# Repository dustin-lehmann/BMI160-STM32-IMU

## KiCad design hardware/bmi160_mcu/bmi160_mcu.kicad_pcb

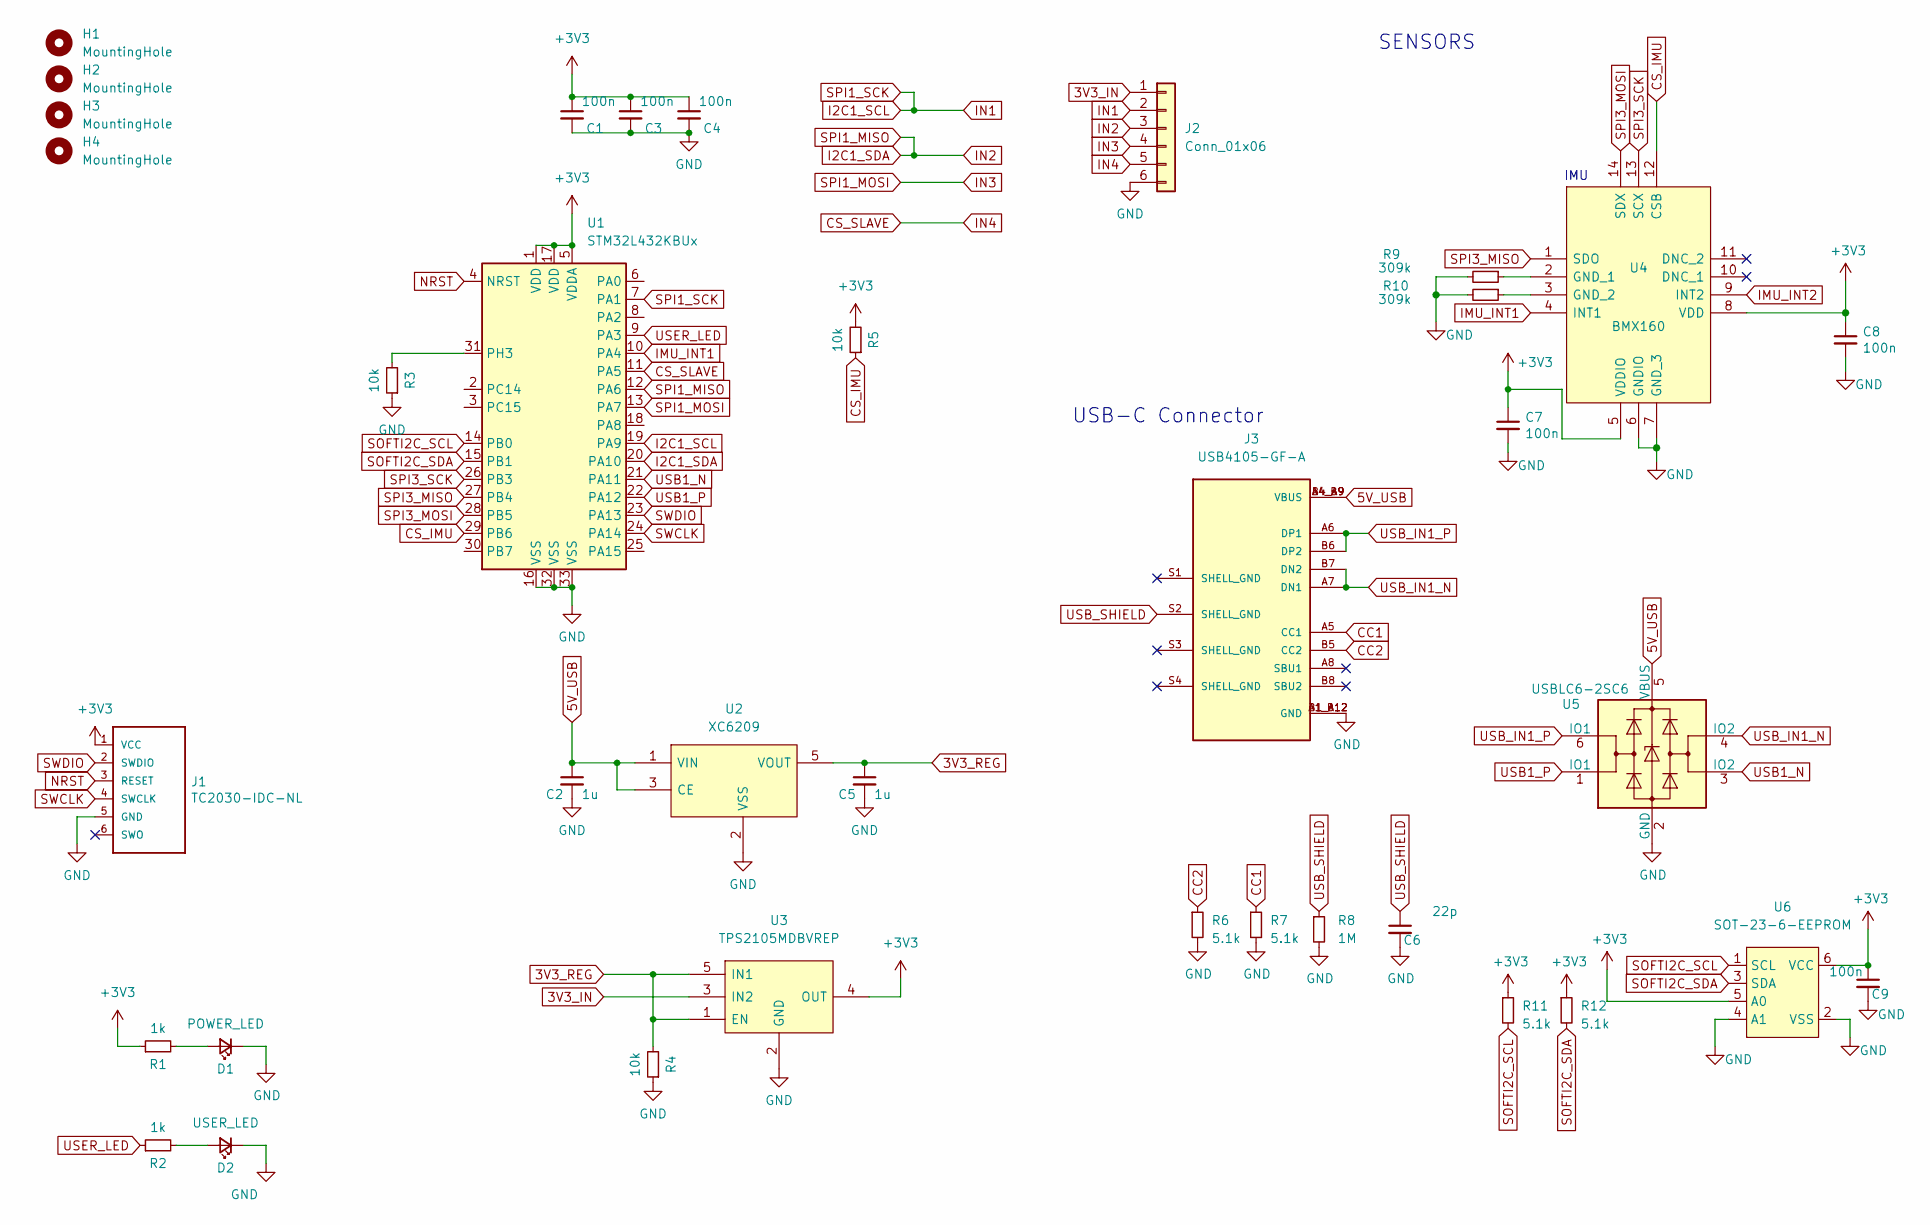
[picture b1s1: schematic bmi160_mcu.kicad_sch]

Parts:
C1, C3, C4, C7, C8, C9: 100n; C_0603_1608Metric
C2, C5: 1u; C_0603_1608Metric
C6: 22p; C_0603_1608Metric
D1: POWER_LED; LED_0603_1608Metric
D2: USER_LED; LED_0603_1608Metric
H1, H2, H3, H4: MountingHole; MH_noPad_2.5
J1: TC2030-IDC-NL; Tag-Connect_TC2030-IDC-NL_2x03_P1.27mm_Vertical
J2: Conn_01x06; JST_GH_SM06B-GHS-TB_1x06-1MP_P1.25mm_Horizontal
J3: USB4105-GF-A; GCT_USB4105-GF-A; PARTREV A3
R1, R2: 1k; R_0603_1608Metric
R3, R4, R5: 10k; R_0603_1608Metric
R6, R7, R11, R12: 5.1k; R_0603_1608Metric
R8: 1M; R_0603_1608Metric
R9, R10: 309k; R_0603_1608Metric
U1: STM32L432KBUx; QFN-32-1EP_5x5mm_P0.5mm_EP3.45x3.45mm
U2: XC6209; SOT95P280X130-5N; Mouser Part Number 865-XC6701B332MR-G
U3: TPS2105MDBVREP; SOT95P280X145-5N; Mouser Part Number 595-TPS2105MDBVREP
U4: BMX160; PQFN50P300X250X88-14N; Mouser Part Number 262-BMX160
U5: USBLC6-2SC6; SOT-23-6
U6: SOT-23-6-EEPROM; SOT-23-6

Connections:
3V3_IN: J2.1, U3.3 (IN2)
3V3_REG: C5.1, R4.2, U2.5 (VOUT), U3.1 (EN), U3.5 (IN1)
5V_USB: C2.1, J3.A4_B9 (VBUS), J3.B4_A9 (VBUS), U2.1 (VIN), U2.3 (CE), U5.5 (VBUS)
+3V3: C1.1, C3.1, C4.1, C7.1, C8.1, C9.1, J1.1 (VCC), R1.1, R5.2, R11.1, R12.1, U1.1 (VDD), U1.5 (VDDA), U1.17 (VDD), U3.4 (OUT), U4.5 (VDDIO), U4.8 (VDD), U6.5 (A0), U6.6 (VCC)
CC1: J3.A5 (CC1), R7.1
CC2: J3.B5 (CC2), R6.1
CS_IMU: R5.1, U1.29 (PB6), U4.12 (CSB)
CS_SLAVE: J2.5, U1.11 (PA5)
GND: C1.2, C2.2, C3.2, C4.2, C5.2, C6.2, C7.2, C8.2, C9.2, D1.1 (K), D2.1 (K), J1.5 (GND), J2.6, J3.A1_B12 (GND), J3.B1_A12 (GND), R3.1, R4.1, R6.2, R7.2, R8.2, R9.2, R10.2, U1.16 (VSS), U1.32 (VSS), U1.33 (VSS), U2.2 (VSS), U3.2 (GND), U4.6 (GNDIO), U4.7 (GND_3), U5.2 (GND), U6.2 (VSS), U6.4 (A1)
I2C1_SCL: J2.2, U1.7 (PA1), U1.19 (PA9)
I2C1_SDA: J2.3, U1.12 (PA6), U1.20 (PA10)
IMU_INT1: U1.10 (PA4), U4.4 (INT1)
IMU_INT2: U4.9 (INT2)
IN3: J2.4, U1.13 (PA7)
NRST: J1.3 (RESET), U1.4 (NRST)
unnamed: D1.2 (A), R1.2
unnamed: D2.2 (A), R2.2
unnamed: R3.2, U1.31 (PH3)
unnamed: R9.1, U4.2 (GND_1)
unnamed: R10.1, U4.3 (GND_2)
SOFTI2C_SCL: R11.2, U1.14 (PB0), U6.1 (SCL)
SOFTI2C_SDA: R12.2, U1.15 (PB1), U6.3 (SDA)
SPI3_MISO: U1.27 (PB4), U4.1 (SDO)
SPI3_MOSI: U1.28 (PB5), U4.14 (SDX)
SPI3_SCK: U1.26 (PB3), U4.13 (SCX)
SWCLK: J1.4 (SWCLK), U1.24 (PA14)
SWDIO: J1.2 (SWDIO), U1.23 (PA13)
USB1_N: U1.21 (PA11), U5.3 (IO2)
USB1_P: U1.22 (PA12), U5.1 (IO1)
USB_IN1_N: J3.A7 (DN1), J3.B7 (DN2), U5.4 (IO2)
USB_IN1_P: J3.A6 (DP1), J3.B6 (DP2), U5.6 (IO1)
USB_SHIELD: C6.1, J3.S2 (SHELL_GND), R8.1
USER_LED: R2.1, U1.9 (PA3)

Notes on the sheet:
SENSORS
IMU
USB-C Connector

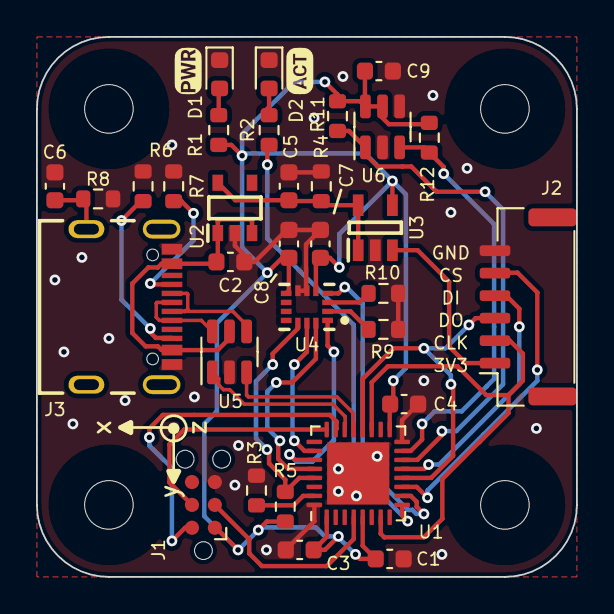
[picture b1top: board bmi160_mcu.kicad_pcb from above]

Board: 2 copper layers, 30.0 x 30.0 mm, 36 parts (0 on the bottom side), 32 nets.

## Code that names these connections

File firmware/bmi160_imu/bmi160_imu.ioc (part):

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Mcu.Name=STM32L432K(B-C)Ux
Mcu.Package=UFQFPN32
Mcu.UserName=STM32L432KBUx
PA1.Mode=Full_Duplex_Master
PA1.Signal=SPI1_SCK
PA10.Mode=Asynchronous
PA10.Signal=USART1_RX
PA13\ (JTMS-SWDIO).Mode=Serial_Wire
PA13\ (JTMS-SWDIO).Signal=SYS_JTMS-SWDIO
PA14\ (JTCK-SWCLK).Mode=Serial_Wire
PA14\ (JTCK-SWCLK).Signal=SYS_JTCK-SWCLK
PA3.GPIOParameters=GPIO_Label
PA3.GPIO_Label=LED
PA3.Signal=GPIO_Output
PA6.Mode=Full_Duplex_Master
PA6.Signal=SPI1_MISO
PA7.Mode=Full_Duplex_Master
PA7.Signal=SPI1_MOSI
PA9.Mode=Asynchronous
PA9.Signal=USART1_TX
PB3\ (JTDO-TRACESWO).Mode=Full_Duplex_Master
PB3\ (JTDO-TRACESWO).Signal=SPI3_SCK
PB4\ (NJTRST).Mode=Full_Duplex_Master
PB4\ (NJTRST).Signal=SPI3_MISO
PB5.Mode=Full_Duplex_Master
PB5.Signal=SPI3_MOSI
PB6.GPIOParameters=GPIO_PuPd
PB6.GPIO_PuPd=GPIO_PULLUP
PB6.Signal=GPIO_Output
RCC.HSE_VALUE=8000000
RCC.SYSCLKFreq_VALUE=80000000
RCC.SYSCLKSource=RCC_SYSCLKSOURCE_PLLCLK
board=custom

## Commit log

2024-03-09 bugfixes
